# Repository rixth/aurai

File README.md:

# aurai

Helping traditional air conditioners join the Internet of Things -  Aurai allows any AC that has a remote control to be controlled via a modern web interface.

This is an entry in to the Hackaday Prize. Details build logs are available on the [project page](https://hackaday.io/project/2288).

## The hardware

Aurai comprises of two hardware components. The first is the base  station (or "hub") which connects to a computer over a USB-UART. The second component, referred to as the "spoke", contains the infrared transmitter to talk to the AC and environmental monitoring sensors. The two units communicate with each other over a wireless connection.

## The software

I have found that many home automation software packages have atrocious interfaces. I tried to ensure that Aurai does not.

## The firmware

The hub & spoke communicate using a series of simple commands over the radio link. The hub should be able to ask the spoke for current environmental data, or to turn on the AC, set target temperature, etc. The spoke firmware contains a state machine to keep track of the air conditioner's state, as some commands are not always valid (ie. you can't set the target temperature when the AC mode is set to "fan only").

## License

Aurai's hardware, firmware & software are licensed under the GPL. The project uses avr-libc extensively, which is under a modified BSD license.

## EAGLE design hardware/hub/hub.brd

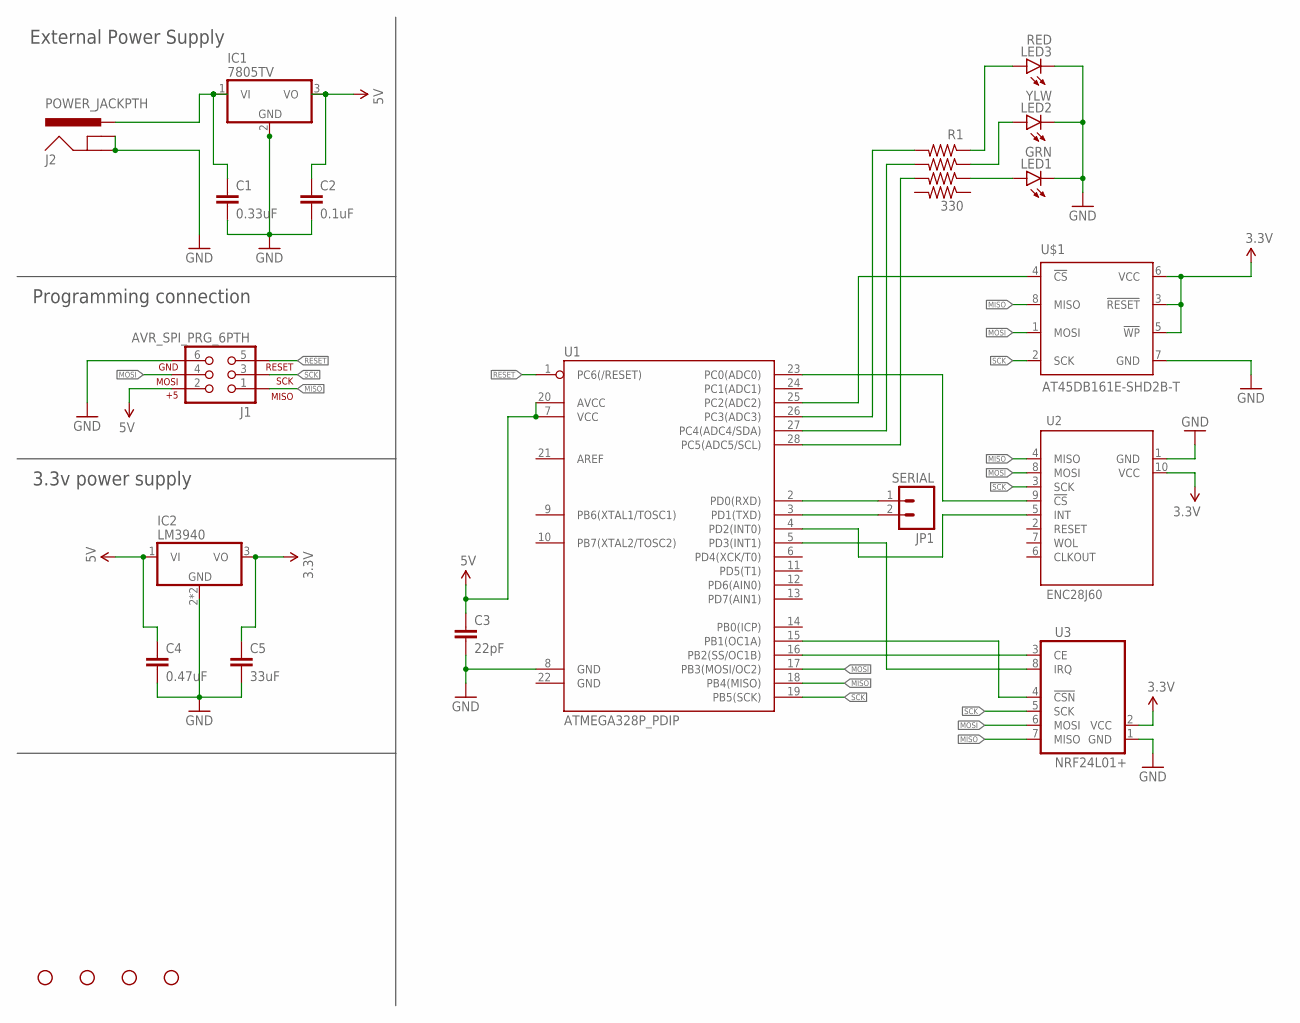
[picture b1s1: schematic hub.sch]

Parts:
C1: 0.33uF; 0805
C2: 0.1uF; 0805
C3: 22pF; 0805
C4: 0.47uF; 0805
C5: 33uF; 0805
IC1: 7805TV; TO220V
IC2: LM3940; SOT223
J1: AVR_SPI_PRG_6PTH; 2X3
J2: POWER_JACKPTH; POWER_JACK_PTH
JP1: SERIAL; 1X02
LED1: GRN; LED-1206
LED2: YLW; LED-1206
LED3: RED; LED-1206
R1: 330; CRA06S08
STANDOFF1, STANDOFF2, STANDOFF3, STANDOFF4: STAND-OFF
U1: ATMEGA328P_PDIP; DIL28-3
U2: ENC28J60; ENC28J60_HEADER
U3: NRF24L01+; NRF24L01_HEADER
U$1: AT45DB161E-SHD2B-T; SO08-EIAJ

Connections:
3.3V: C5.1, IC2.3 (VO), U2.10 (VCC), U3.2 (VCC), U$1.3 (!RESET), U$1.5 (!WP), U$1.6 (VCC)
5V: C2.1, C3.1, C4.1, IC1.3 (VO), IC2.1 (VI), J1.2, U1.7 (VCC), U1.20 (AVCC)
GND: C1.2, C2.2, C3.2, C4.2, C5.2, IC1.2 (GND), IC2.2 (GND), IC2.4 (GND), J1.6, J2.GND, J2.GNDBREAK, LED1.C, LED2.C, LED3.C, U1.8 (GND), U2.1 (GND), U3.1 (GND), U$1.7 (GND)
MISO: J1.1, U1.18 (PB4(MISO)), U2.4 (MISO), U3.7 (MISO), U$1.8 (MISO)
MOSI: J1.4, U1.17 (PB3(MOSI/OC2)), U2.8 (MOSI), U3.6 (MOSI), U$1.1 (MOSI)
unnamed: LED1.A, R1.3 (R3A)
unnamed: JP1.1, U1.2 (PD0(RXD))
unnamed: R1.7 (R2B), U1.27 (PC4(ADC4/SDA))
unnamed: JP1.2, U1.3 (PD1(TXD))
unnamed: R1.8 (R1B), U1.26 (PC3(ADC3))
unnamed: LED3.A, R1.1 (R1A)
unnamed: U1.15 (PB1(OC1A)), U3.4 (!CSN)
unnamed: LED2.A, R1.2 (R2A)
unnamed: U1.16 (PB2(SS/OC1B)), U3.3 (CE)
unnamed: U1.5 (PD3(INT1)), U3.8 (IRQ)
unnamed: U1.25 (PC2(ADC2)), U$1.4 (!CS)
unnamed: R1.6 (R3B), U1.28 (PC5(ADC5/SCL))
unnamed: U1.23 (PC0(ADC0)), U2.9 (!CS)
unnamed: C1.1, IC1.1 (VI), J2.PWR
unnamed: U1.4 (PD2(INT0)), U2.5 (INT)
RESET: J1.5, U1.1 (PC6(/RESET))
SCK: J1.3, U1.19 (PB5(SCK)), U2.3 (SCK), U3.5 (SCK), U$1.2 (SCK)

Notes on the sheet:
External Power Supply
Programming connection
3.3v power supply

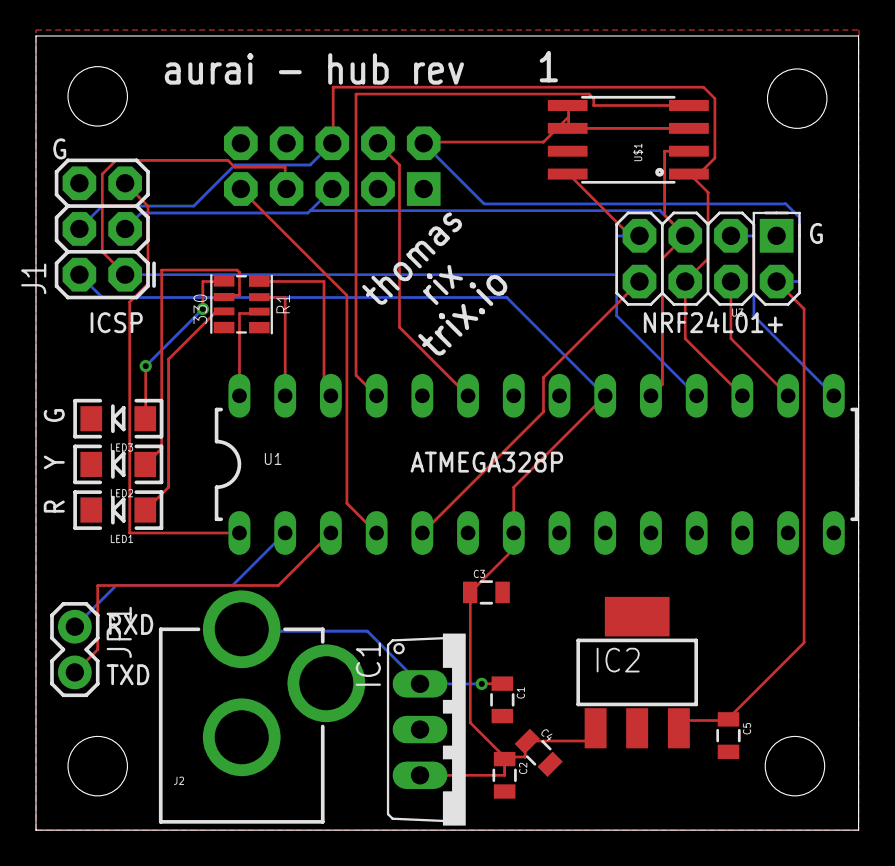
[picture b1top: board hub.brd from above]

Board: 2 copper layers, 45.7 x 44.1 mm, 22 parts (1 on the bottom side), 22 nets.

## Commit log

2014-08-06 Structure
2014-08-06 Add gitignore for Eagle
2014-08-06 Empty schematics for the hub and spoke
2014-08-07 Initial library part for AT25M01 in SOIC adapter
2014-08-07 Put some bits on a schematic
2014-08-08 Add SOIC-8 EIAJ footprint, and AT25M01 package for it
2014-08-08 Add NRF24L01+ breakout header
2014-08-08 Update spoke schematic
2014-08-08 DHT-11 breakout part
2014-08-08 Schematic update for spoke. Added DHT-11 and LEDS
2014-08-08 Fix bad wiring in PSU
2014-08-08 Beginnings of a board
2014-08-09 MOAR SMDs and 3.3v supply fixes
2014-08-09 Bunch o' shared module code
2014-08-09 The start of Spoke firmware1
2014-08-09 Add SerialIO_hasData
2014-08-09 Test code for SerialIO_hasData manipulating LEDs
2014-08-10 No leading 0s on SerialIO_putb
2014-08-10 Change how the pindefines works
2014-08-10 A time function
2014-08-10 DHT-11 sensor reading
2014-08-10 DHT11 library no longer needs micros function
2014-08-10 Loop over all serial data at once
2014-08-10 Fix warning
2014-08-10 Add serial command to makefile
2014-08-10 Clean share dir too
2014-08-10 Move EEPROM_CS and make sure we use the defined pin
2014-08-10 Add ctags to gitignore
2014-08-10 Ignore autorouter logs
2014-08-10 IR send implementation
2014-08-10 Diag test code
2014-08-10 Update schematic from todos
2014-08-11 Adjust schematic. Begin routing.
2014-08-11 Finish routing spoke!
2014-08-11 Remove AT25M01 EEPROM from Spoke
2014-08-11 Add real 3.3v LDO regulator
2014-08-11 Add resistor array and LM3904 parts
2014-08-12 Update spoke board
2014-08-12 Bump spoke revision to 2
2014-08-13 Fix up EEPROM includes
2014-08-13 NRF24L01 radio code
2014-08-14 EEPROM should modify a buffer
2014-08-14 Add SerialIO_puth
2014-08-14 Update radio code
2014-08-15 Add ENC28J60 part
2014-08-15 Add AT45DB161E part
2014-08-15 Move from LM3490 to LM3940 regulator
2014-08-16 Use rn's
2014-08-16 Use proper newlines
2014-08-16 Radio test that works!
2014-08-16 This PWM code messes /w OC2A too (MISO).
    Not sure why this is, but so I'm turning the timer on and off completly.
    In the future, I'll move the LED to a different timer.
2014-08-17 Object-based serial class
2014-08-17 Move to object-based SPI
2014-08-17 DiagLED functions
2014-08-17 Move test to inside their respective function files
2014-08-17 Remove tests not used on spoke
2014-08-17 Hub source code
2014-08-17 Test radio transmission using the DiagLEDs
2014-08-17 Move SPI eeprom code in to the hub source
2014-08-17 Rename EEPROM to Flash since that's what it is
2014-08-17 Internal EEPROM access
2014-08-17 AirConditioner control model
2014-08-17 Add NRF24_fetch function to get payload
2014-08-17 Add NRF24_flush()
2014-08-17 Fix warning in Serial
2014-08-17 Working wireless link to toggle the AC!
2014-08-17 Testing sending data back from the spoke
2014-08-17 A rudimetary control panel
2014-08-17 Spoke command definition
2014-08-18 Complete the text-based UI for the hub
2014-08-18 Move command line to its own file
2014-08-18 Move initialization of radio to its own function in the spoke
2014-08-18 Use dynamic payload length
2014-08-18 Move AC code to shared so we can use its constants
2014-08-18 Better status reporting with more datA
2014-08-18 User interface mock
2014-08-18 Some helpful constants for spoke status
2014-08-18 Serial interface
2014-08-19 Makefile to help with two projects
2014-08-19 Add reset fuction
2014-08-19 Send command success/fail back
2014-08-19 Pretty printing of status
2014-08-19 Change command for command line
2014-08-19 Set the radios to do lots of retries /w a big delay
2014-08-19 New booting code for spoke
2014-08-19 Save/restore AC state. Green LED on first boot.
2014-08-19 Handle more commands
2014-08-19 Add data sizes to output
2014-08-19 Betting logging of a bad status report
2014-08-19 Actually send a \n rather than a \r\n
2014-08-19 Take advantage of the diagnostic LEDs
2014-08-19 Annotate command file
2014-08-19 Use LEDs to indicate boot mode
2014-08-19 Operator error.
2014-08-19 Memory corruption is real kids.
    The test functions have so many strings in them that it was killing the
    DATA memory.
2014-08-19 Break out env and status in to separate commands
2014-08-19 Tidy up the boot process
2014-08-19 Noob bitwise logic error
2014-08-19 Fix macros for extracting info from status bits
2014-08-19 Tidy up command line responses
2014-08-19 Always send our status back
2014-08-19 Web API
2014-08-19 WOWWW. Working web interface!
2014-08-19 Drain before returning
2014-08-19 Properly validate fan speed requests
2014-08-19 > is not the same as <
2014-08-19 UI improvements
2014-08-19 If we timeout, actually return...
    ... don't just spam the serial port with 0x03
2014-08-19 Up the serial timeout
2014-08-20 Put commands in a queue to be processed to avoid messing up the serial communication
2014-08-20 Cast arguments to the correct type
2014-08-20 Changes to make server<->hub communication slightly more robust
2014-08-20 SerialInterface doesn't lock anymore
2014-08-20 Set up a timer that increases a seconds counter
2014-08-20 Environmental logger
2014-08-20 Command to dump env log
2014-08-20 Move strings to PGM memory. Holy RAM savings!
2014-08-20 Define for EL debugging
2014-08-20 Collect data less often
2014-08-20 WAY cleaner node<->hub communication
2014-08-20 Read the environment log data
2014-08-20 Only YOU can prevent forest crashes
2014-08-20 Increase env log interval
2014-08-20 Unbreak the build
2014-08-20 XHR and style cleanup
2014-08-20 Report trends in the user interface
2014-08-20 Add reset link
2014-08-21 New look
2014-08-21 Put scripts back on to interfacE
2014-08-21 Disable items as applicable
2014-08-21 Visual tweaks and add fastclick
2014-08-21 Schematic PDFs
2014-08-21 Don't use a \n based parser for incoming data
2014-08-21 Payload back from hub now specifies its length.
    No more relying on parsing \r\n!
2014-08-25 Fix flash pinout. Finish hub brd
2014-08-26 Change pins for the real versions
2014-08-26 Just do env logging to EEPROM for now...
2014-08-26 Flash diag LEDs at first start

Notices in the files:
parts and their libraries:
SparkFun-DigitalIC: Licensing: Creative Commons ShareAlike 4.0 International - https://creativecommons.org/licenses/by-sa/4.0
